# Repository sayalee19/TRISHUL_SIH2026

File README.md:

## Ready Prototype Images
<table width="100%" style="border-collapse: collapse; border: none;">
  <tr>
    <!-- Left Image and Caption -->
    <td align="left" style="border: none; width: 50%;">
      <br>
      <small>RATH</small>
    </td>
    <!-- Right Image and Caption -->
    <td align="right" style="border: none; width: 50%;">
      <br>
      <small>RATH- Internal View</small>
    </td>
  </tr>
</table>
<table width="100%" style="border-collapse: collapse; border: none;">
  <tr>
    <!-- Left Image and Caption -->
    <td align="left" style="border: none; width: 50%;">
      <br>
      <small>MUKUT</small>
    </td>
    <!-- Right Image and Caption -->
    <td align="right" style="border: none; width: 50%;">
      <br>
      <small>SAARTHI</small>
    </td>
  </tr>
</table>

<br clear="both" />

<div align="center" style="margin-top: 20px;">
  
  <br>
  <small>Overview of the Website Dashboard</small>
</div>

## Problem Statement
To assist rescue teams during emergencies in underground coal mines, providing them with real time information of the underground conditions and reducing response delays.

## Solution Proposed

Underground coal mining remains one of the most hazardous industrial environments in the world, and the danger compounds sharply the moment something goes wrong. Toxic gas accumulation, flooding, tunnel or roof collapse, and near-zero visibility are everyday operational risks, but the real crisis begins after an incident: rescue teams typically have to enter an area they know almost nothing about, using safety infrastructure that was often destroyed in the same event they're responding to. TRISHUL is built around the observation that the mine already has plenty of monitoring and communication equipment, but almost all of it depends on fixed wiring and infrastructure, which means it fails at exactly the moment it's needed most, when a tunnel collapse severs it. TRISHUL's design goal is to build a system that keeps functioning after the primary infrastructure has been physically destroyed. The name reflects this directly-  like a trident, the system is only complete and effective when its three separate units work together as one weapon against the problem, rather than as three independent gadgets.

Unit One:  Mukut (the worn identity and locator unit). Mukut is a helmet-mounted module worn continuously by every miner during their shift. It serves two distinct functions that solve different problems and use different mechanisms. The first is live tracking: each Mukut unit periodically broadcasts a short low-power beacon signal using ESPNOW broadcast mode using an ESP32C3 (containing its unique ID) that nearby Sarthi nodes pick up. This periodic broadcast is deliberately low-frequency (on the order of once every few minutes) to conserve battery across a full shift, and the broadcast timing includes a small randomised jitter so that if two helmets happen to power on at nearly the same moment, they don't end up permanently transmitting in lockstep and repeatedly colliding. The second function is physical identification during actual recovery. If a miner is unconscious, or their helmet's battery has died, or the local network is down, there is no live signal to query. For this reason, Mukut also carries a passive NFC/RFID tag, which requires no onboard power at all and can be read by a rescuer's handheld reader simply by being close to it- carrying the worker's ID,, and any critical medical flags. This is a deliberate, low-power fallback layered underneath the active tracking system.

Unit Two: Sarthi (the fixed monitoring and mesh backbone). Sarthi nodes are installed at intervals along the mine's tunnels, at positions that are surveyed and recorded once during installation. They perform three jobs simultaneously. First, they listen for Mukut beacons and report what they hear to the surface, which is how miner location is estimated. To receive the Mukut beacons, they have ESP32 in receive mode for ESPNOW broadcast. Sarthi nodes do trilateration- two or three nearby nodes each report the signal strength (RSSI) at which they received the same beacon, the surface system can combine these readings to produce a rough position estimate, generally biased toward whichever node heard the signal strongest. 
Second, Sarthi continuously monitors the mine environment using onboard sensors- general-purpose gas sensors for baseline monitoring, and seismic/vibration sensors capable of detecting the ground motion associated with a roof or tunnel failure. Rather than streaming raw sensor values constantly, each node processes its readings locally and only raises a flag when values move meaningfully beyond an established baseline, thus keeping  routine network traffic small and making genuine anomalies stand out clearly at the surface dashboard. 
Third, Sarthi nodes relay all of this information- miner locations and sensor flags, hop by hop through a self-organising wireless mesh network back to a surface gateway. This mesh is designed so that no single node is a single point of failure for everything behind it: each node simply broadcasts what it knows, listens for what its neighbours are broadcasting, and forwards new information onward, using packet IDs and a hop-limit to prevent the same message being endlessly re-broadcast in loops. If a node goes offline, its neighbours simply stop hearing from it and traffic reroutes through whatever alternative path still exists, without needing to be manually reconfigured. A collapse event is inferred not from a single sensor reading in isolation, but from a correlated pattern- several adjacent Sarthi nodes going silent at once, together with a seismic spike reported by nodes still alive nearby. 
These Sarthi nodes are powered normally through the power cables that are already present in the mines. They also have an additional battery backup in case the power lines are disrupted in an event of a collapse.

Unit Three: Rath (the autonomous rescue rover). Rath is only deployed after the surface command centre confirms a likely collapse event or gas leak from the Sarthi network's combined signals. It is a tracked rover specifically chosen over wheels because tracks distribute weight and maintain traction across loose rubble and uneven collapsed terrain, which wheeled platforms handle poorly. For navigation, Rath uses LIDAR-based SLAM (simultaneous localisation and mapping), allowing it to build a live map of the collapsed area as it drives and navigate autonomously without needing a pre-existing map of the zone. 
Rath carries a dedicated multi-gas sensing unit, distinct from Sarthi's generic sensors, because at this stage the mission needs precise, gas-specific readings rather than a simple threshold flag. This unit detects CO, CH4, propane, ammonia, and H2S individually, and an onboard processor calculates standard occupational safety metrics- IDLH (Immediately Dangerous to Life or Health) and STEL (Short-Term Exposure Limit) values, directly from these readings using established formulas, so that rescue teams receive an already-interpreted hazard assessment rather than raw numbers they'd have to manually cross-reference.
Rath also carries a thermal camera and a standard visual camera; because visibility underground after a collapse is often extremely poor (dust, smoke, low light), the video and thermal streams are processed by AI-based image restoration/enhancement algorithms at the surface, to improve usability for both the human operators watching the feed and any onboard person-detection algorithms trying to automatically spot survivors in the footage, rather than relying solely on a human operator to notice something in a degraded feed.
All the measurements and visuals obtained from the Rath as well as the miner locations obtained from the Mukut and transmitted via Sarthi network would then be visible on a central dashboard at the surface, in real time.

TRISHUL proposes a resilient, layered safety and rescue architecture designed to remain operational when conventional mine infrastructure is compromised. By integrating Mukut's persistent worker identification and localisation, Sarthi's distributed environmental monitoring and self-organising communication backbone, and Rath's autonomous reconnaissance and hazard-assessment capabilities, the system establishes a continuous chain from detection and localisation to assessment and response. Its distributed architecture ensures that the failure of individual nodes or communication links does not necessarily result in the failure of the entire system, while the combination of active and passive identification, local sensor intelligence, mesh communication, autonomous mapping, multi-gas analysis, and enhanced visual and thermal perception provides redundancy across multiple stages of an emergency. Rather than attempting to replace existing mine safety infrastructure, TRISHUL is designed as a resilient layer that takes over when that infrastructure becomes unavailable. Ultimately, the system aims to reduce uncertainty during the most critical phase of a mining disaster, enabling rescue teams to understand where the incident has occurred, what hazards are present, and how the affected area can be approached before human responders are exposed to unnecessary risk.

## Technical Approach

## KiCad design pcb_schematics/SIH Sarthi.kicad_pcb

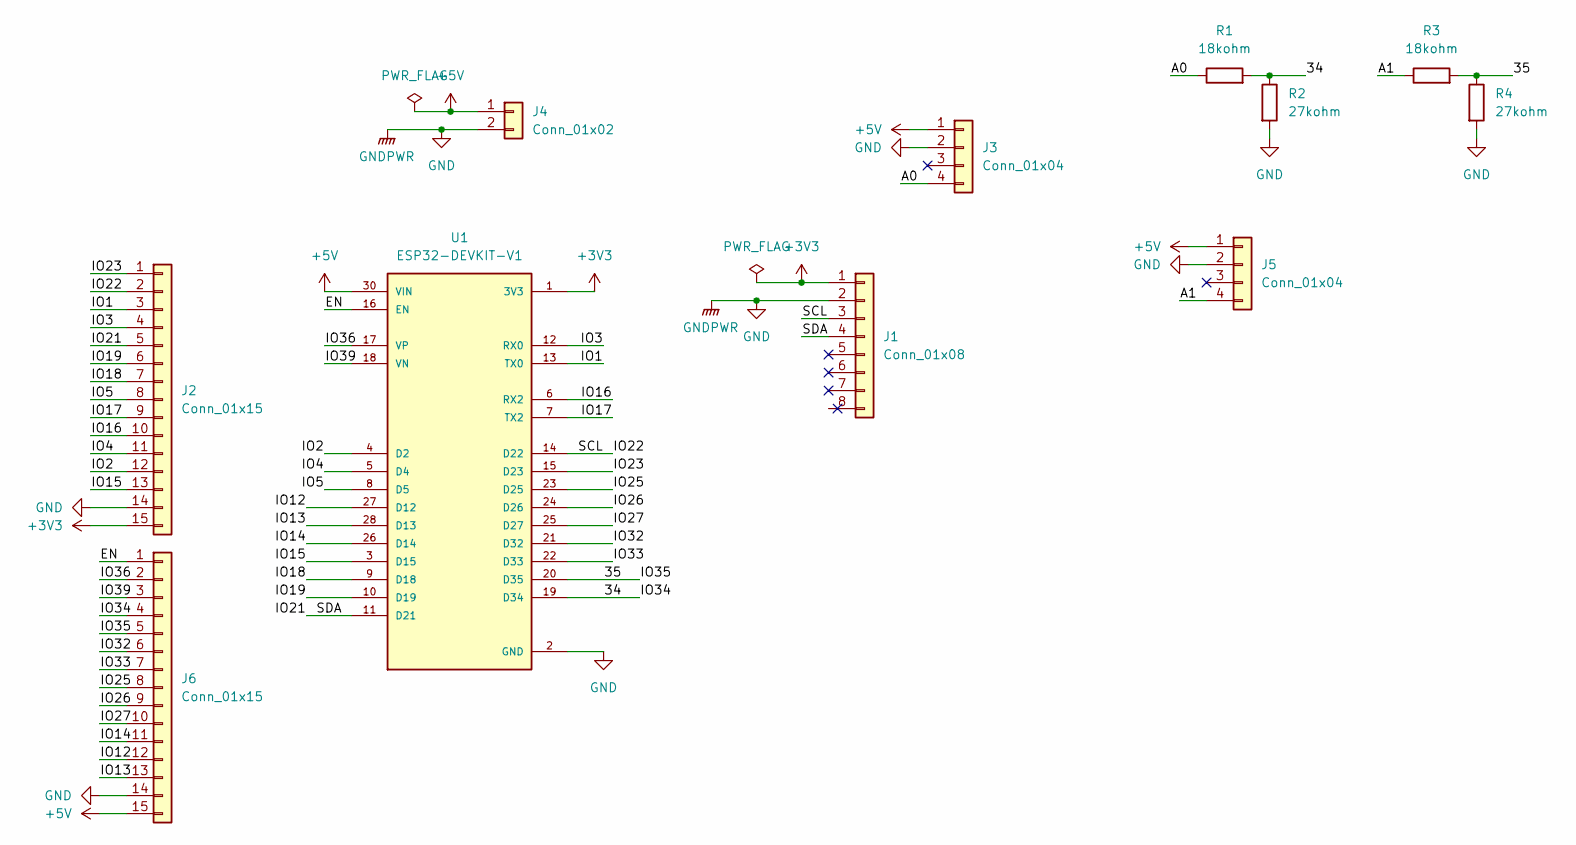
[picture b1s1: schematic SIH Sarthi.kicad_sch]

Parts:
J1: Conn_01x08; PinHeader_1x08_P2.54mm_Vertical
J2, J6: Conn_01x15; PinHeader_1x15_P2.54mm_Vertical
J3, J5: Conn_01x04; PinHeader_1x04_P2.54mm_Vertical
J4: Conn_01x02; PinSocket_1x02_P2.54mm_Vertical
R1, R3: 18kohm; R_Axial_DIN0207_L6.3mm_D2.5mm_P5.08mm_Vertical
R2, R4: 27kohm; R_Axial_DIN0207_L6.3mm_D2.5mm_P5.08mm_Vertical
U1: ESP32-DEVKIT-V1; MODULE_ESP32_DEVKIT_V1; PARTREV N/A

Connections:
+3V3: J1.1, J2.15, U1.1 (3V3)
+5V: J3.1, J4.1, J5.1, J6.15, U1.30 (VIN)
/34: J6.4, R1.2, R2.1, U1.19 (D34)
/35: J6.5, R3.2, R4.1, U1.20 (D35)
/A0: J3.4, R1.1
/A1: J5.4, R3.1
/EN: J6.1, U1.16 (EN)
/IO1: J2.3, U1.13 (TX0)
/IO2: J2.12, U1.4 (D2)
/IO3: J2.4, U1.12 (RX0)
/IO4: J2.11, U1.5 (D4)
/IO5: J2.8, U1.8 (D5)
/IO12: J6.12, U1.27 (D12)
/IO13: J6.13, U1.28 (D13)
/IO14: J6.11, U1.26 (D14)
/IO15: J2.13, U1.3 (D15)
/IO16: J2.10, U1.6 (RX2)
/IO17: J2.9, U1.7 (TX2)
/IO18: J2.7, U1.9 (D18)
/IO19: J2.6, U1.10 (D19)
/IO21: J1.4, J2.5, U1.11 (D21)
/IO22: J1.3, J2.2, U1.14 (D22)
/IO23: J2.1, U1.15 (D23)
/IO25: J6.8, U1.23 (D25)
/IO26: J6.9, U1.24 (D26)
/IO27: J6.10, U1.25 (D27)
/IO32: J6.6, U1.21 (D32)
/IO33: J6.7, U1.22 (D33)
/IO36: J6.2, U1.17 (VP)
/IO39: J6.3, U1.18 (VN)
GND: J1.2, J2.14, J3.2, J4.2, J5.2, J6.14, R2.2, R4.2, U1.2 (GND), U1.29 (GND)

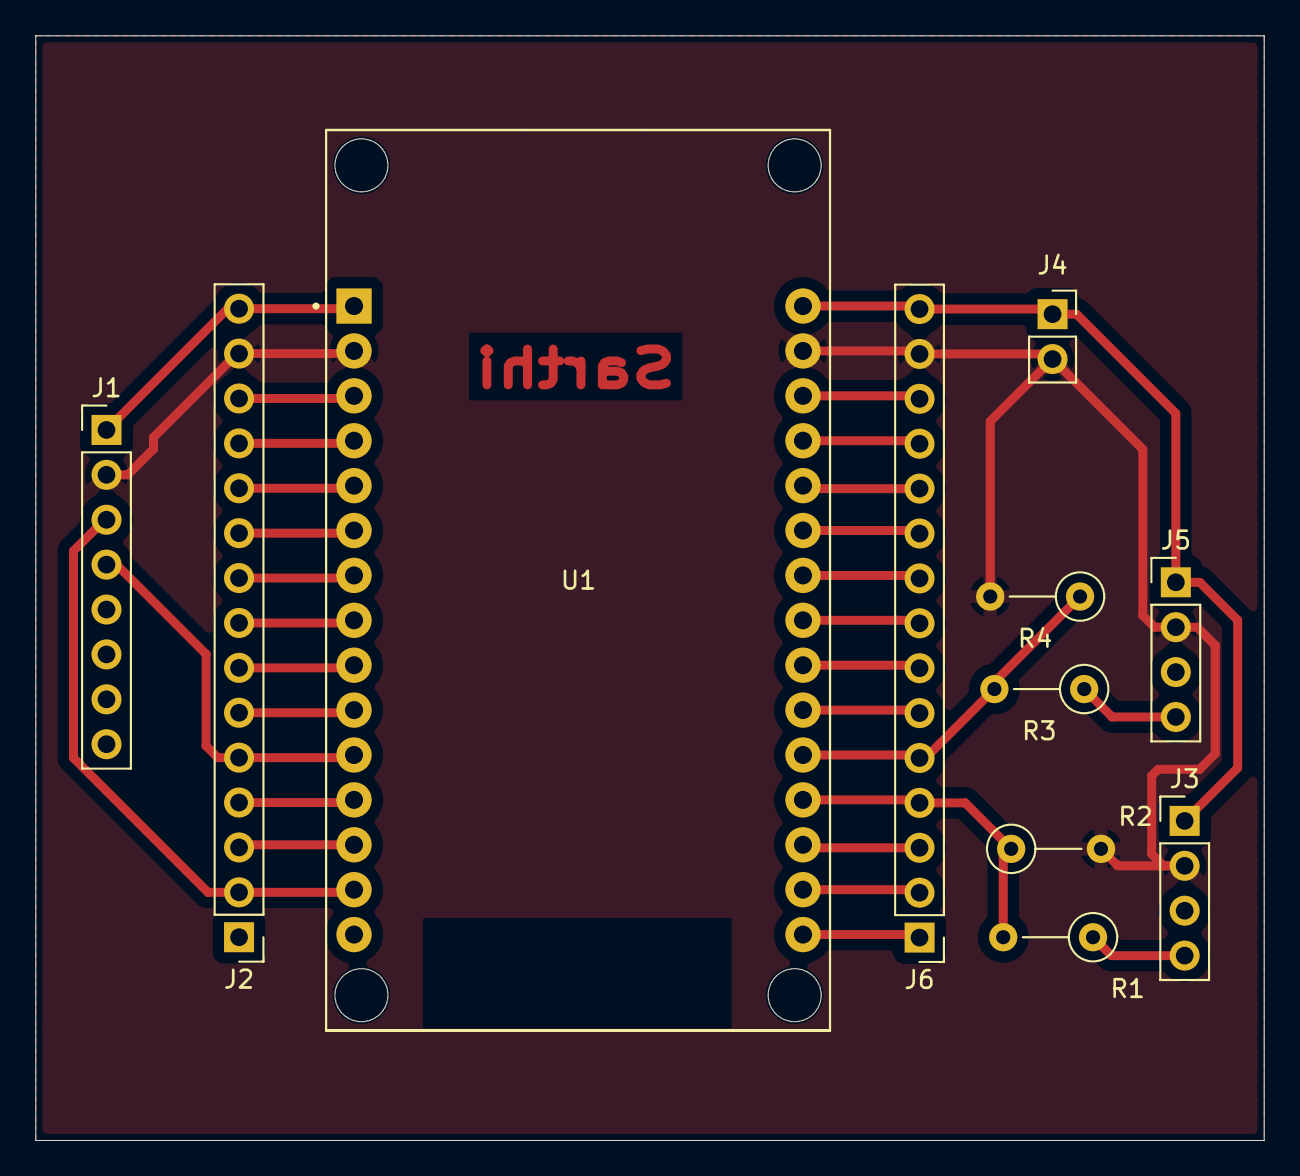
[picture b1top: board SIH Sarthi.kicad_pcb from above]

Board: 2 copper layers, 69.5 x 62.5 mm, 11 parts (0 on the bottom side), 31 nets.
